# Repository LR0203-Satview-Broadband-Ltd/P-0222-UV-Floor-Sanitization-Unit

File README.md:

# P-0222 | UV Floor Sanitization Unit

> Low-voltage custom PCB replacing an Arduino-based prototype for a hospital UV floor sanitization platform.

| Project | Status | Current package | Owner |
| --- | --- | --- | --- |
| P-0222 | Released | First Release v1 package complete and ready for supplier release | Ing. Vega Maximiliano |

## Project Overview

Satview Broadband Ltd. is developing a UV foot-sanitizing floor unit for hospital environments. This project replaces the prototype controller with a professional PCB that manages the UV cycle, relay actuation, protected 24 VDC input, power regulation, timer selection, and external component connections.

The current released baseline for the project is the PRD v1.1 package in `project_docs/requirements/PRD v1.1.md`. The design remains under Logic Reliance engineering processes and follows the project requirements, acceptance criteria, and KiCad library governance defined for the work.

## Current Status

The PCB, schematic, and manufacturing reviews were completed. First Release v1 was completed on 2026-08-28 and is ready for supplier release. Review updates include the C5, C7, and C12 part numbers and the D1 and R7 values and part numbers. Review records remain available in `project_docs/requirements/Reviews.md`.

### Package Contents

- BOM: 40 grouped entries and 70 component references.
- Assembly positions: pick-and-place files generated; DNP handling is recorded in the BOM and review notes.
- Component sourcing: manufacturer, MPN, and DigiKey fields populated in the current EBOM.
- Fabrication outputs: Gerbers, ODB++, PTH/NPTH drills, assembly files, drawings, and 3D model present.
- Surface finish: `ENEPIG`.
- Board UID and board specifications added to the `F.Fab` layer and assembly drawing.
- Manufacturing drill outputs: duplicate PTH/NPTH files removed.
- Logic Reliance BOM workbook: editable Excel version generated from the KiCad CSV.

## Technical Scope

- Requirements traceability and acceptance criteria.
- Electrical sizing and power regulation validation.
- STM32C011F6 MCU control.
- Relay-driven UV load switching.
- Reverse-polarity, surge, fuse, and transient protection.
- Configurable cycle timer through DIP switches.
- KiCad schematic capture, PCB layout, manufacturing outputs, and supporting evidence.

## Design Boundaries

This iteration includes the low-voltage PCB only.

Out of scope:

- 120 VAC design, which remains within the external certified power supply.
- Mechanical enclosure design.
- Regulatory certification.
- UV strip sourcing and final optical characterization.

## Manufacturing Package

The manufacturing package is delivered as:

`pcb_0222/outputs/Manufacture/20260828-P_0222_manufacture.zip`

| Directory or file | Purpose |
| --- | --- |
| `Manufacture.Files.rev20280828.zip` | Manufacturing files package |
| `Design.Files.rev20280828.zip` | Design source files |
| `EBOM.rev202608288.xlsx` | Logic Reliance electronic BOM |
| `Mechanical.outputs.rev20280828.zip` | Mechanical outputs |
| `schematics.rev20280828.pdf` | Schematic PDF |
| `Top.View.rev2080828.png` | Board top-view image |

The complete First Release v1 package is available at `pcb_0222/outputs/Releases/v1_20260828/`.

## Repository Contents

This is the controlled inventory of publishable project content. Local process notes, AI working files, and internal assistant configuration are intentionally excluded from publication.

| Directory | Contents |
| --- | --- |
| `pcb_0222/` | KiCad project, schematic, PCB, local library assets, and manufacturing outputs |
| `project_docs/design/` | MCU boot, pinout, power supply, and implementation records |
| `project_docs/datasheets/` | Manufacturer datasheets and component package evidence |
| `project_docs/references/` | External technical references used for engineering decisions |
| `project_docs/requirements/` | Released PRD and processor requirements |

### Design Records

- `mcu_boot/`
- `mcu_pinout/`
- `power_supply/`

### Datasheet Categories

`buttons/` · `conectors/` · `debugger/` · `dipswitch/` · `inductor/` · `leds/` · `mcu/` · `nails/` · `npn/` · `pmos/` · `pptc/` · `psu/` · `relay/` · `rotary/` · `tvs/` · `xtal/` · `zenner/`

Some directory names preserve legacy spelling for traceability, including `conectors/` and `zenner/`.

## Key Documents

- [Project context baseline](p-0222.md)
- [Released PRD](project_docs/requirements/PRD%20v1.1.md)
- [Processor requirements](project_docs/requirements/Processor%20Requirements.md)
- [MCU boot and programming records](project_docs/design/mcu_boot/)
- [MCU pinout records](project_docs/design/mcu_pinout/)
- [Power supply records](project_docs/design/power_supply/)

## General Project Updates

- 2026-07-27: KiCad project files were uploaded and the schematic baseline was published.
- 2026-07-28: SWD programming guidance and STM32C0 BOOT0 handling were documented.
- 2026-07-29: Footprint and datasheet review entered the active validation cycle.
- 2026-07-30: Placement outputs, drawings, STEP model, and exchange artifacts were refreshed.
- 2026-08-02: Schematic review comments were incorporated into the PCB and manufacturing outputs.
- 2026-08-09: Layout placement and routing review continued with synchronized schematic and PCB updates.
- 2026-08-11: The active layout iteration was prepared for formal review.
- 2026-08-16: A preliminary manufacturing package was generated to support the pending layout review.
- 2026-08-16: Board UID and board specifications were added to the `F.Fab` layer and assembly drawing to improve manufacturing traceability.
- 2026-08-18: Repository documentation was refreshed to align the README, project baseline, and automation instructions with the current PRD v1.1 status and the pending formal layout review.
- 2026-08-27: Layout review passed; C5, C7, and C12 part numbers and D1 and R7 values and part numbers were updated.
- 2026-08-28: PCB, schematic, and manufacturing reviews were completed; First Release v1 artifacts were generated under `pcb_0222/outputs/Releases/v1_20260828/`.
- 2026-09-17: The `SP1103C-01UTG` schematic symbol was updated, with the related schematic and PCB project files synchronized.

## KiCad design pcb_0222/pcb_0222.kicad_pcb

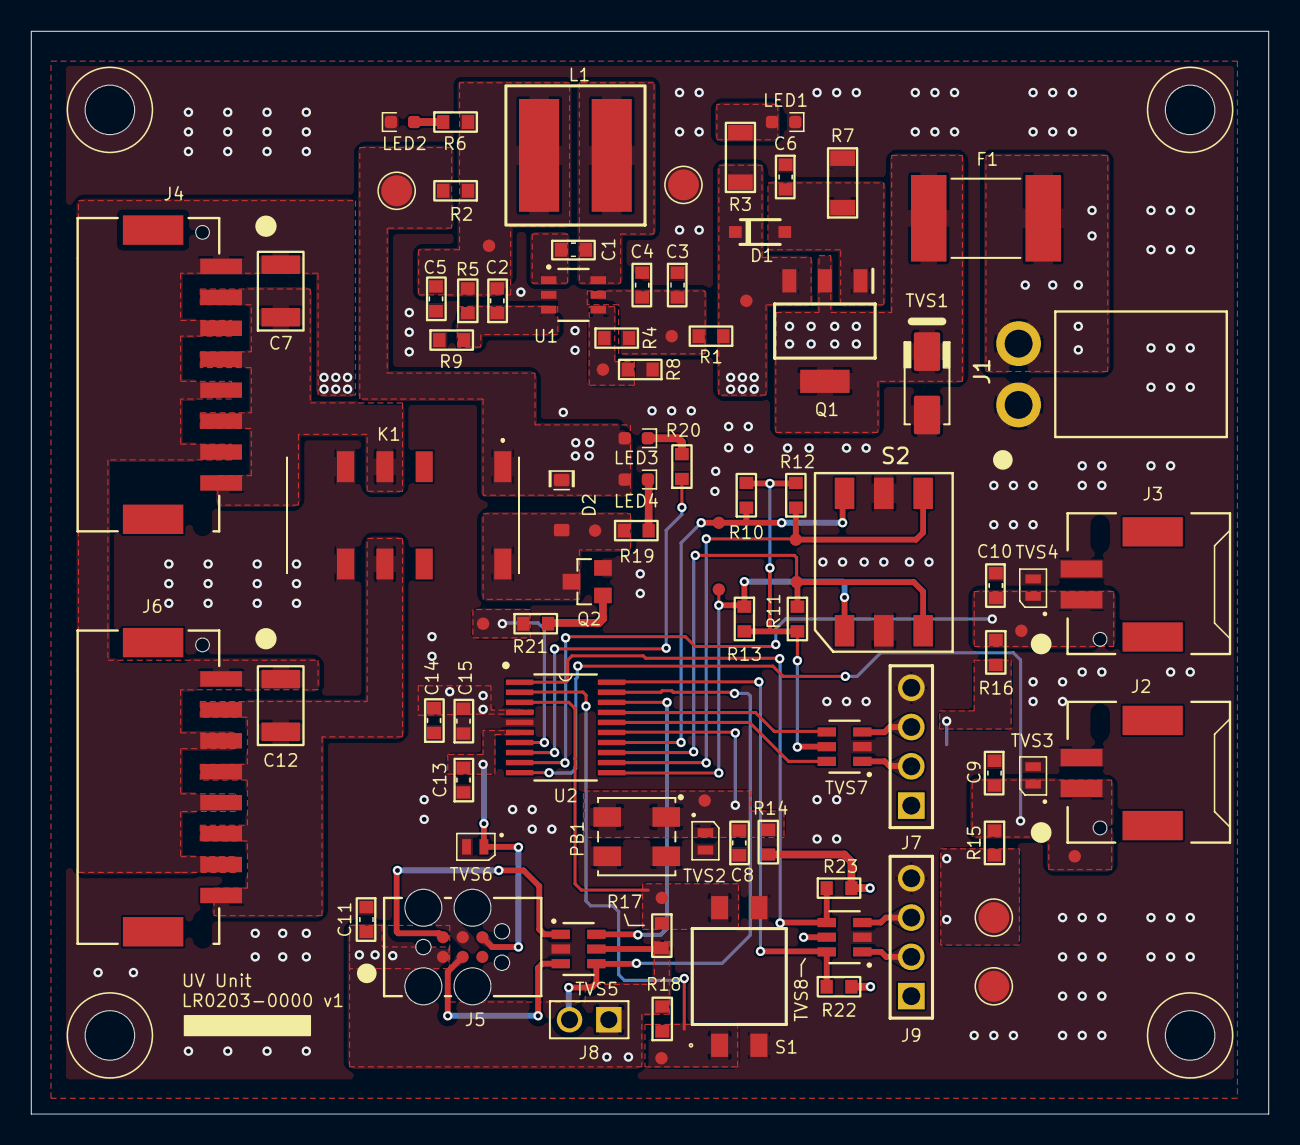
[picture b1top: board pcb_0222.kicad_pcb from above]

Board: 2 copper layers, 80.0 x 70.0 mm, 94 parts (0 on the bottom side), 44 nets.

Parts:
C1, C4, C6, C11, C13, C14: 100nF; C_0603
C2: 1pF; C_0603
C3, C15: 4.7uF; C_0603
C5: 10uF; C_0603
C7, C12: 10uF; C_1210_TDK_CGA6_2.8mm_Tall
C8, C9, C10: 10nF; C_0603
D1: BZT52C5V1; SOD-123F
D2: 40V 1A; B5819W
F1: 60V 1A; 0ZCF0100AF2A
J1: S2P-VH
J2, J3: SM02B-PASS-TBT
J4, J6: SM08B-PASS-TBT
J5: TC-2030-IDC; TC2030-IDC
J7, J9: HEADER_MALE_THT_0.1"_4x1; 61300411121
J8: HEADER_MALE_THT_0.1"_2x1; 77311-118-02LF
K1: EE2-3NUH; EE23NUH
L1: 12uH; L_44.88mm3_6.8x6.8mm_Bourns_SRR6038-120Y
LED1, LED2: LTST-C190GKT; LED_0603
LED3: LTST-C190KSKT; LED_0603
LED4: LTST-C190KRKT; LED_0603
M1, M2, M3, M4: mounting_hole_M3_NPTH
PB1: 7914J-1-000
Q1: BSP170PH6327XTSA1; SOT-223-4
Q2: BC817-16; SOT-23-3
R1, R2: 0R; R_0603
R3: 2.2K; R_1206
R4: 2.87M; R_0603
R5: 69.8K; R_0603
R6, R19, R20: 120R; R_0603
R7: 3.6K; R_1206
R8: 200K; R_0603
R9: 22.1K; R_0603
R10, R11, R12, R13, R14, R15, R16, R17, R18: 10K; R_0603
R21: 1K; R_0603
R22, R23: 4K7; R_0603
S1: DS04-254-2-02BK-SMT-TR
S2: CD10RM0SB
TP1, TP2, TP3, TP4: TP_SMD_2mm
TP5, TP6, TP7, TP8, TP9, TP10, TP11, TP12, TP13, TP14, TP15, TP16, TP17, TP18, TP19: TP_SMD_0.8mm
TVS1: 26V; DO-214AC
TVS2, TVS3, TVS4, TVS6: 3V3; 2-DFN_(1.6x1)
TVS5, TVS7, TVS8: USBLC6-2SC6; SOT-23-6 [2.8x2.93x1.1,P=0.95]mm
U1: LMR54406DBVR; SOT-23-6
U2: STM32C011F6P6; TSSOP-20 [6.4x4.4x1.2,P=0.65]mm

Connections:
+3V3: C11.2, C14.2, C15.2, D2.C, J5.1 (VREF), J7.1, J8.1, J9.1, K1.1 (COIL+), LED3.A, LED4.A, R2.2, R10.2, R11.2, R12.2, R13.2, R14.2, R15.2, R16.2, R17.2, R18.2, R22.2, R23.2, TP3.1, TP4.1, TVS5.5 (VBUS), TVS7.5 (VBUS), TVS8.5 (VBUS), U2.4 (VDD/VDDA)
/FB: C2.1, R5.1, R9.2, U1.3 (FB)
/MCU_BCD0: R13.1, S2.1, TP9.1, U2.11 (PA4)
/MCU_BCD1: R12.1, S2.2, TP13.1, U2.12 (PA5)
/MCU_BCD2: R11.1, S2.4, TP15.1, U2.13 (PA6)
/MCU_BCD3: R10.1, S2.8, TP17.1, U2.14 (PA7)
/MCU_DIP1: R18.1, S1.1, TP14.1, U2.2 (PC14-OSCX_IN)
/MCU_DIP2: R17.1, S1.3, TP16.1, U2.3 (PC15-OSCX_OUT)
/MCU_LED: R20.1, U2.8 (PA1)
/MCU_RELAY: R21.1, TP19.1, U2.7 (PA0)
/MCU_SW1: C10.2, J3.1, R16.1, TP12.1, TVS4.C, U2.9 (PA2)
/MCU_SW2: C9.2, J2.1, R15.1, TP11.1, TVS3.C, U2.10 (PA3)
/MCU_TEST: C8.2, PB1.1, PB1.2, R14.1, TP10.1, TVS2.C, U2.15 (PA8)
/NRST: C13.2, J5.6 (NRST), TVS6.C, U2.6 (PF2-NRST)
/RX1: TVS7.4 (I/O2), U2.17 (PA12[PA10])
/SCL1: R23.1, TVS8.4 (I/O2), U2.1 (PB7)
/SDA1: R22.1, TVS8.6 (I/O1), U2.20 (PB6)
/SW: C1.2, L1.1, U1.6 (SW)
/SWCLK: J8.2, TVS5.4 (I/O2), U2.19 (PA14-BOOT0)
/SWDIO: TVS5.6 (I/O1), U2.18 (PA13)
/TX1: TVS7.6 (I/O1), U2.16 (PA11[PA9])
GND: C3.1, C4.1, C5.1, C6.1, C8.1, C9.1, C10.1, C11.1, C13.1, C14.1, C15.1, J1.1, J2.2, J3.2, J5.4 (GND), J7.4, J9.4, K1.5 (NO_1), K1.8 (NO_2), LED1.K, LED2.K, PB1.3, PB1.4, Q2.2 (E), R7.1, R8.1, R9.1, S1.2, S1.4, S2.C1, S2.C2, TP1.1, TP2.1, TVS1.A, TVS2.A, TVS3.A, TVS4.A, TVS5.2 (GND), TVS6.A, TVS7.2 (GND), TVS8.2 (GND), U1.2 (GND), U2.5 (VSS/VSSA)
unnamed: C2.2, C5.2, L1.2, R2.1, R5.2, R6.2, TP7.1
unnamed: C6.2, D1.A, Q1.1, R7.2
unnamed: F1.1, Q1.2 (D), Q1.4 (D), TVS1.C
unnamed: J5.3 (SWCLK), TVS5.3 (I/O2)
unnamed: J5.2 (SWDIO), TVS5.1 (I/O1)
unnamed: J7.2, TVS7.1 (I/O1)
unnamed: J7.3, TVS7.3 (I/O2)
unnamed: J9.2, TVS8.1 (I/O1)
unnamed: J9.3, TVS8.3 (I/O2)
unnamed: D2.A, K1.12 (COIL-), Q2.3 (C), R19.1, TP18.1
unnamed: C7.1, J4.2, J4.4, J4.6, J4.8, K1.4 (COM_1)
unnamed: C12.1, J6.2, J6.4, J6.6, J6.8, K1.9 (COM_2)
unnamed: LED1.A, R3.1
unnamed: LED2.A, R6.1
unnamed: LED3.K, R20.2
unnamed: LED4.K, R19.2
unnamed: Q2.1 (B), R21.2
unnamed: C1.1, U1.1 (CB)
unnamed: R4.1, R8.2, TP8.1, U1.4 (EN)
unnamed: C3.2, C4.2, R1.2, R4.2, TP6.1, U1.5 (VIN)
VB: F1.2, J1.2
VB_IP: C7.2, C12.2, D1.C, J4.1, J4.3, J4.5, J4.7, J6.1, J6.3, J6.5, J6.7, Q1.3 (S), R1.1, R3.2, TP5.1
